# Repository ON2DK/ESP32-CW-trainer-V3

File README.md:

# ESP32 CW Trainer V3

Standalone ESP32-based CW/Morse trainer PCB for paddle and straight-key practice.

## V3 hardware revision

V3 standardizes the external connectors on real PCB-mounted parts instead of generic connector placeholders:

- **J4 DC input:** GCT DCJ200-10-A horizontal THT barrel jack
- **J10 Paddle:** CUI/Same Sky SJ1-3533NG 3.5 mm TRS jack
- **J11 Audio/headphone:** CUI/Same Sky SJ1-3533NG 3.5 mm TRS jack
- **J14 Straight Key:** CUI/Same Sky SJ1-3533NG 3.5 mm TRS jack

### Jack wiring

| Connector | Tip | Ring | Sleeve |
|---|---|---|---|
| J10 Paddle | DIT | DAH | GND |
| J11 Audio | Audio via 100 ohm | Audio via 100 ohm | GND |
| J14 Straight Key | STRAIGHT_KEY | Not connected | GND |

J4 uses pin 1 for the DC input to F1, pin 2 for GND, and pin 3 (internal switch contact) is intentionally unused.

## Main hardware

- ESP32-WROOM-32 / 38-pin DevKit footprint
- TFT interface
- Paddle input
- Straight-key input
- Rotary encoder with push switch
- LM386 audio amplifier
- Buzzer
- Volume control
- 12 V external input
- 500 mA resettable fuse
- TRACO TSR 1-2450 5 V regulator

## Design status

As of **19 September 2026**:

- KiCad: **10.0.4**
- ERC: **0 errors, 0 warnings**
- DRC: **0 violations**
- Unconnected PCB items: **0**
- Schematic parity problems: **0**
- Gerber production set regenerated after the V3 connector changes
- Hardware assembly/testing: **pending**

Two intentional ERC exceptions remain documented in the project: the project-specific ESP32 symbol/library difference and the GPIO34 input-only ADC check.

## Production files

The clean all-THT Gerber package contains:

- F.Cu / B.Cu
- F.Mask / B.Mask
- F.Silkscreen / B.Silkscreen
- Edge.Cuts
- PTH drill
- NPTH drill
- .gbrjob

Paste layers are not required for this THT board.

## Recommended repository files

- KiCad schematic (`.kicad_sch`)
- KiCad PCB (`.kicad_pcb`)
- KiCad project (`.kicad_pro`)
- Gerber ZIP
- Arduino firmware (`.ino`)
- Project logbook with BOM and photos
- PCB / schematic / 3D images

## Notes

Before ordering, inspect the final Gerbers in the PCB manufacturer's viewer, especially J4, J10, J11, J14, mounting holes and Edge.Cuts.

This project is currently electrically/design-rule checked, but the V3 hardware has not yet been validated on an assembled PCB.

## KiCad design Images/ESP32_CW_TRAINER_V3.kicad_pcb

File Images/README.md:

# Images

Afbeeldingen van schema, PCB, 3D-weergave en de later opgebouwde hardware.

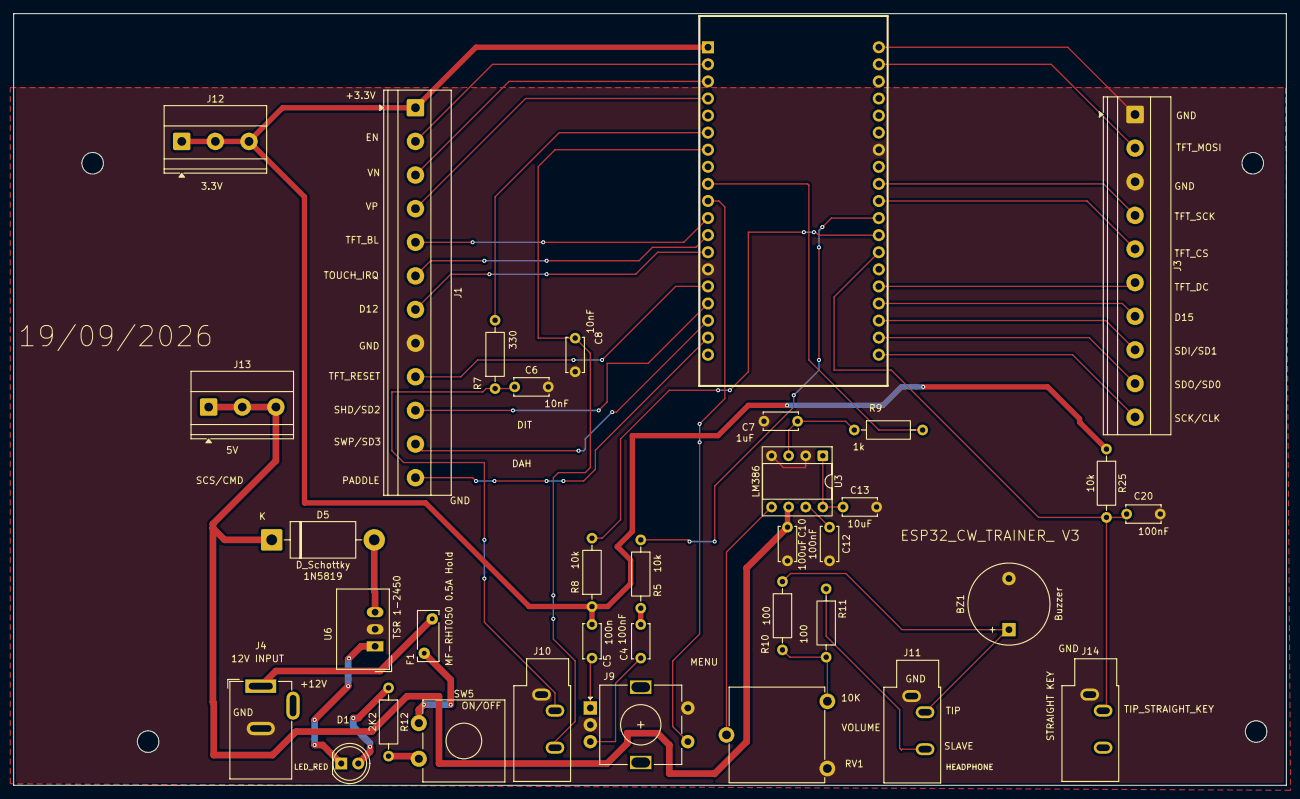
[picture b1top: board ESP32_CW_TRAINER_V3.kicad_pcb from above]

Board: 2 copper layers, 189.2 x 114.8 mm, 35 parts (0 on the bottom side), 45 nets.

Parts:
BZ1: Buzzer; Buzzer_12x9.5RM7.6
C4, C12, C20: 100nF; C_Disc_D5.0mm_W2.5mm_P5.00mm
C5: 100n; C_Disc_D5.0mm_W2.5mm_P5.00mm
C6, C8: 10nF; C_Disc_D5.0mm_W2.5mm_P5.00mm
C7: 1uF; C_Disc_D5.0mm_W2.5mm_P5.00mm
C10: 100uF; C_Disc_D5.0mm_W2.5mm_P5.00mm
C13: 10uF; C_Disc_D5.0mm_W2.5mm_P5.00mm
D1: LED_RED; LED_D5.0mm
D5: D_Schottky; D_DO-201AD_P15.24mm_Horizontal
F1: MF-RHT050 0.5A Hold; Fuse_Bourns_MF-RHT050
J1: Conn_01x12; TerminalBlock_Phoenix_MKDS-1,5-12_1x12_P5.00mm_Horizontal
J3: Conn_01x10; TerminalBlock_Phoenix_MKDS-1,5-10_1x10_P5.00mm_Horizontal
J4: Barrel_Jack_Switch; BarrelJack_GCT_DCJ200-10-A_Horizontal
J9: RotaryEncoder_Switch; RotaryEncoder_Alps_EC11E-Switch_Vertical_H20mm
J10, J11, J14: AudioJack3; Jack_3.5mm_CUI_SJ1-3533NG_Horizontal
J12, J13: Conn_01x03; TerminalBlock_Phoenix_MKDS-1,5-3_1x03_P5.00mm_Horizontal
R5, R8, R25: 10k; R_Axial_DIN0207_L6.3mm_D2.5mm_P10.16mm_Horizontal
R7: 330; R_Axial_DIN0207_L6.3mm_D2.5mm_P10.16mm_Horizontal
R9: 1k; R_Axial_DIN0207_L6.3mm_D2.5mm_P10.16mm_Horizontal
R10, R11: 100; R_Axial_DIN0207_L6.3mm_D2.5mm_P10.16mm_Horizontal
R12: 2K2; R_Axial_DIN0207_L6.3mm_D2.5mm_P10.16mm_Horizontal
RV1: 10K; Potentiometer_ACP_CA14V-15_Vertical
SW5: POWER ON/OFF; SW_CW_GPTS203211B
U2: ESP32-WROOM-32; ESP32_DevKit_38P
U3: LM386; DIP-8_W7.62mm_Socket
U6: TSR 1-2450; Converter_DCDC_TRACO_TSR-1_THT

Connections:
+3.3V: C5.1, J1.1, J12.1, J12.2, J12.3, R8.1, R25.1, U2.2 (VDD)
+5V: C10.1, D5.1 (K), J13.1, J13.2, J13.3, U3.6 (V+)
/AUDIO: R9.2, U2.10 (IO25)
/D12: J1.7, U2.14 (IO12)
/D15: J3.7, U2.23 (IO15)
/DAH: C8.1, J10.R, U2.8 (IO32)
/DIT: R7.2, U2.7 (IO35)
/EN: J1.2, U2.3 (EN)
/ENC_A: R8.2, U2.27 (IO16)
/ENC_B: R5.1, U2.28 (IO17)
/ENC_SW: J9.S1, U2.11 (IO26)
/SCK/CLK: J3.10, U2.20 (SCK/CLK)
/SCS/CMD: J1.12, U2.19 (SCS/CMD)
/SDI/SD1: J3.8, U2.22 (SDI/SD1)
/SDO/SD0: J3.9, U2.21 (SDO/SD0)
/SHD/SD2: J1.10, U2.17 (SHD/SD2)
/STRAIGHT_KEY: C20.1, J14.T, R25.2, U2.26 (IO4)
/SWP/SD3: J1.11, U2.18 (SWP/SD3)
/TFT_BL: J1.5, U2.12 (IO27)
/TFT_CS: J3.5, U2.29 (IO5)
/TFT_DC: J3.6, U2.24 (IO2)
/TFT_MOSI: J3.2, U2.37 (IO23)
/TFT_RESET: J1.9, U2.16 (IO13)
/TFT_SCK: J3.4, U2.30 (IO18)
/TOUCH_IRQ: J1.6, U2.13 (IO14)
/VN: J1.3, U2.4 (SENSOR_VP)
/VP: J1.4, U2.5 (SENSOR_VN)
GND: BZ1.2 (-), C6.2, C7.1, C8.2, C10.2, C12.2, C13.2, C20.2, J1.8, J3.1, J3.3, J4.2, J9.C, J9.S2, J10.S, J11.S, J14.S, RV1.3, U2.1 (GND), U2.15 (GND), U2.38 (GND), U3.2 (-), U3.4 (GND), U6.2 (GND)
unnamed: BZ1.1 (+), J11.T, R10.1
unnamed: C4.1, R5.2
unnamed: C4.2, J9.B
unnamed: C5.2, J9.A
unnamed: C6.1, J10.T, R7.1
unnamed: C13.1, U3.1 (GAIN), U3.8 (GAIN)
unnamed: D1.2 (A), R12.1
unnamed: D1.1 (K), U6.1 (IN)
unnamed: D5.2 (A), U6.3 (OUT)
unnamed: F1.2, J4.1
unnamed: J11.R, R11.1
unnamed: R10.2, R11.2, RV1.1
unnamed: RV1.2, U3.5
unnamed: F1.1, SW5.1 (A)
unnamed: R12.2, SW5.2 (B)
unnamed: C7.2, R9.1, U3.3 (+)
unnamed: C12.1, U3.7 (BYPASS)

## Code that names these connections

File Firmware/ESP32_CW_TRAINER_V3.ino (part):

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  Encoder DT      GPIO17
  Encoder SW      GPIO26

  Paddle DIT      GPIO35
  Paddle DAH      GPIO32
  Straight key    GPIO4

  Audio/Buzzer    GPIO25
*/

#include <SPI.h>
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// HARDWARE
// ============================================================

#define TFT_SCK         18
#define TFT_MOSI        23
#define TFT_DC           2
#define TFT_RST         13
#define TFT_CS           5
#define TFT_BACKLIGHT   27

#define BUZZER_PIN      25
#define PADDLE_DIT      35
#define PADDLE_DAH      32
#define STRAIGHT_KEY     4

#define ENCODER_CLK     16
#define ENCODER_DT      17
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  // The TRAINER V2 PCB must therefore provide the external bias for DIT.
  pinMode(PADDLE_DIT, INPUT);
  pinMode(PADDLE_DAH, INPUT_PULLUP);
  pinMode(STRAIGHT_KEY, INPUT_PULLUP);
  pinMode(ENCODER_SW, INPUT_PULLUP);

  pinMode(TFT_BACKLIGHT, OUTPUT);
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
